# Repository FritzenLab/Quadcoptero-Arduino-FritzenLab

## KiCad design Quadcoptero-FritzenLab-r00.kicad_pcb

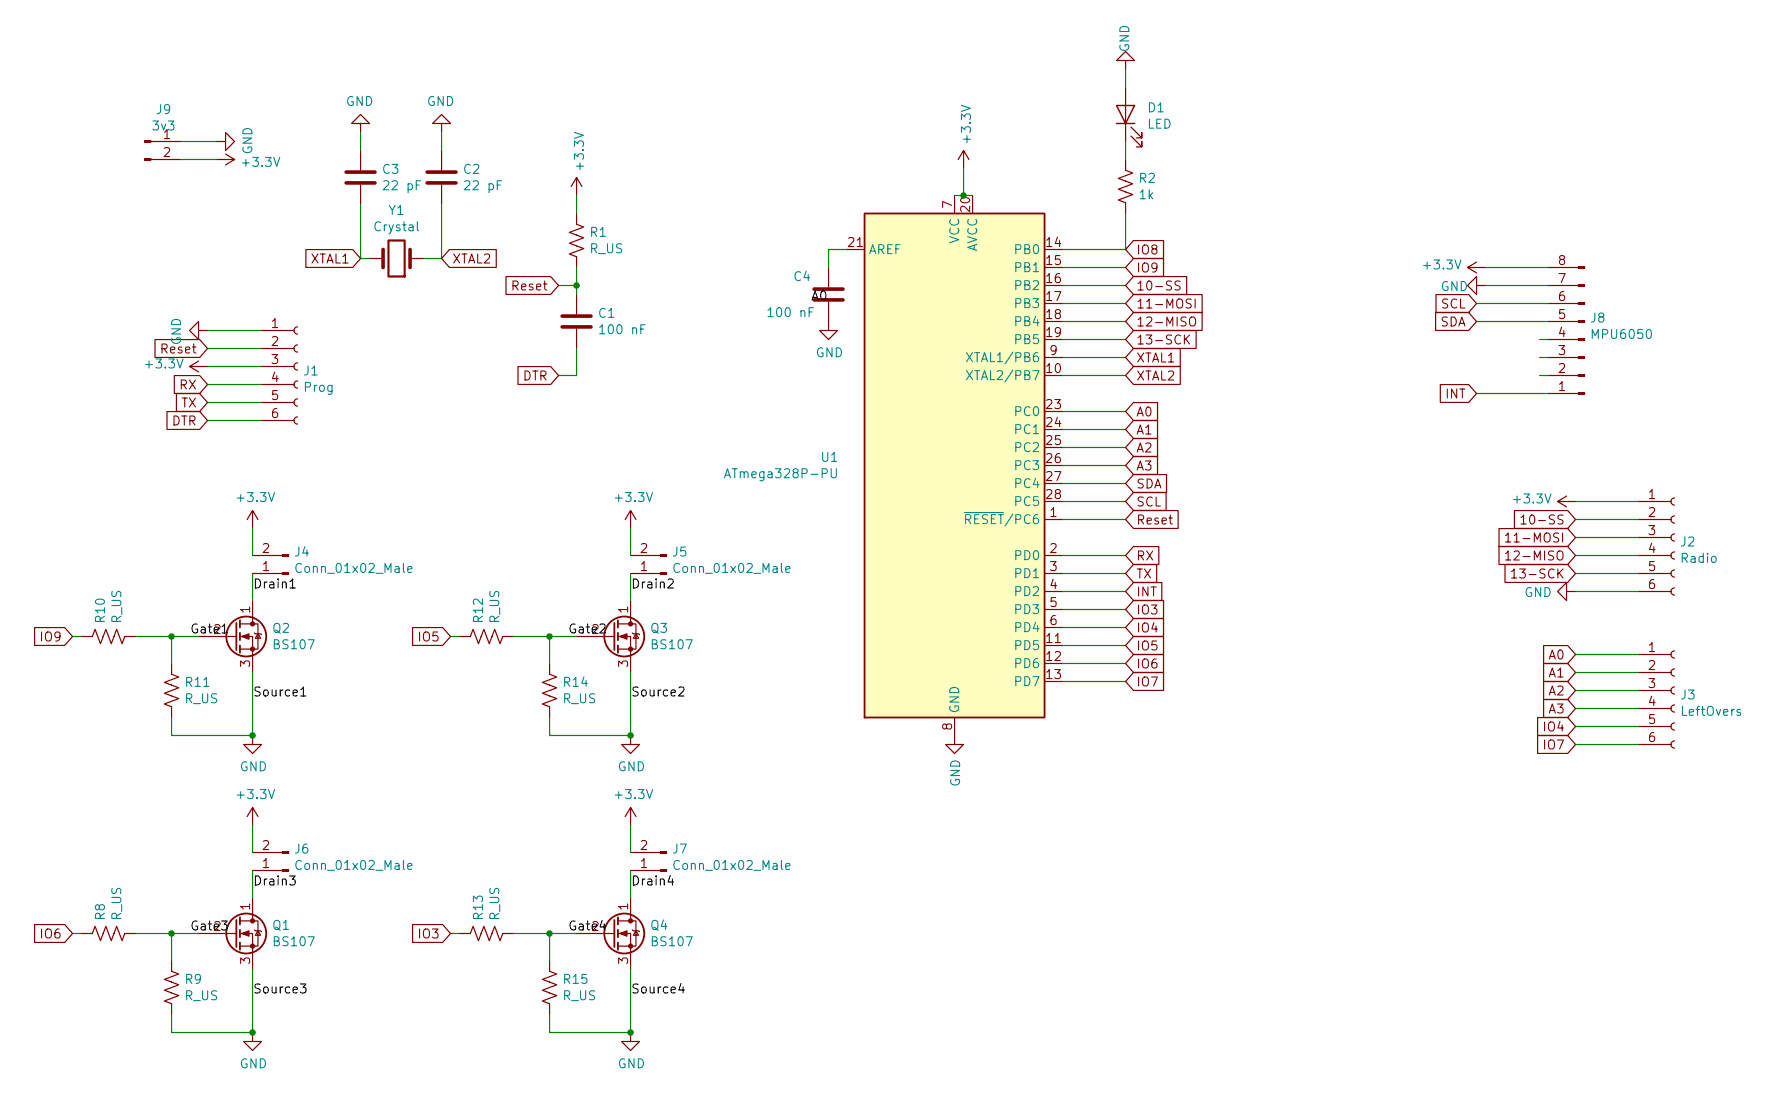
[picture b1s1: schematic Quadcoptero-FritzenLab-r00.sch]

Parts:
C1, C4: 100 nF; C_Disc_D3.0mm_W1.6mm_P2.50mm
C2, C3: 22 pF; C_Disc_D3.0mm_W1.6mm_P2.50mm
D1: LED; LED_D3.0mm
J1: Prog; PinHeader_1x06_P2.54mm_Vertical
J2: Radio; PinHeader_1x06_P2.54mm_Vertical
J3: LeftOvers; PinHeader_1x06_P2.54mm_Vertical
J4, J5, J6, J7: Conn_01x02_Male; PinSocket_1x02_P2.54mm_Vertical
J8: MPU6050; PinHeader_1x08_P2.54mm_Vertical
J9: 3v3; PinHeader_1x02_P2.00mm_Vertical
Q1, Q2, Q3, Q4: BS107; SOT-23W
R1, R8, R9, R10, R11, R12, R13, R14, R15: R_US; R_0805_2012Metric_Pad1.15x1.40mm_HandSolder
R2: 1k; R_0805_2012Metric_Pad1.15x1.40mm_HandSolder
U1: ATmega328P-PU; DIP-28_W7.62mm
Y1: Crystal; Crystal_HC50_Vertical

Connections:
10-SS: J2.2, U1.16 (PB2)
11-MOSI: J2.3, U1.17 (PB3)
12-MISO: J2.4, U1.18 (PB4)
13-SCK: J2.5, U1.19 (PB5)
+3V3: J1.3, J2.1, J4.2, J5.2, J6.2, J7.2, J8.8, J9.2, R1.1, U1.7 (VCC), U1.20 (AVCC)
/Drain1: J4.1, Q2.1 (D)
/Drain2: J5.1, Q3.1 (D)
/Drain3: J6.1, Q1.1 (D)
/Drain4: J7.1, Q4.1 (D)
/Gate1: Q2.2 (G), R10.2, R11.1
/Gate2: Q3.2 (G), R12.2, R14.1
/Gate3: Q1.2 (G), R8.2, R9.1
/Gate4: Q4.2 (G), R13.2, R15.1
A0: J3.1, U1.23 (PC0)
A1: J3.2, U1.24 (PC1)
A2: J3.3, U1.25 (PC2)
A3: J3.4, U1.26 (PC3)
DTR: C1.2, J1.6
GND: C2.1, C3.1, C4.2, D1.2 (A), J1.1, J2.6, J8.7, J9.1, Q1.3 (S), Q2.3 (S), Q3.3 (S), Q4.3 (S), R9.2, R11.2, R14.2, R15.2, U1.8 (GND), U1.22 (GND)
INT: J8.1, U1.4 (PD2)
IO3: R13.1, U1.5 (PD3)
IO4: J3.5, U1.6 (PD4)
IO5: R12.1, U1.11 (PD5)
IO6: R8.1, U1.12 (PD6)
IO7: J3.6, U1.13 (PD7)
IO8: R2.2, U1.14 (PB0)
IO9: R10.1, U1.15 (PB1)
unnamed: C4.1, U1.21 (AREF)
unnamed: D1.1 (K), R2.1
RX: J1.4, U1.2 (PD0)
Reset: C1.1, J1.2, R1.2, U1.1 (~RESET~/PC6)
SCL: J8.6, U1.28 (PC5)
SDA: J8.5, U1.27 (PC4)
TX: J1.5, U1.3 (PD1)
XTAL1: C3.2, U1.9 (XTAL1/PB6), Y1.2
XTAL2: C2.2, U1.10 (XTAL2/PB7), Y1.1

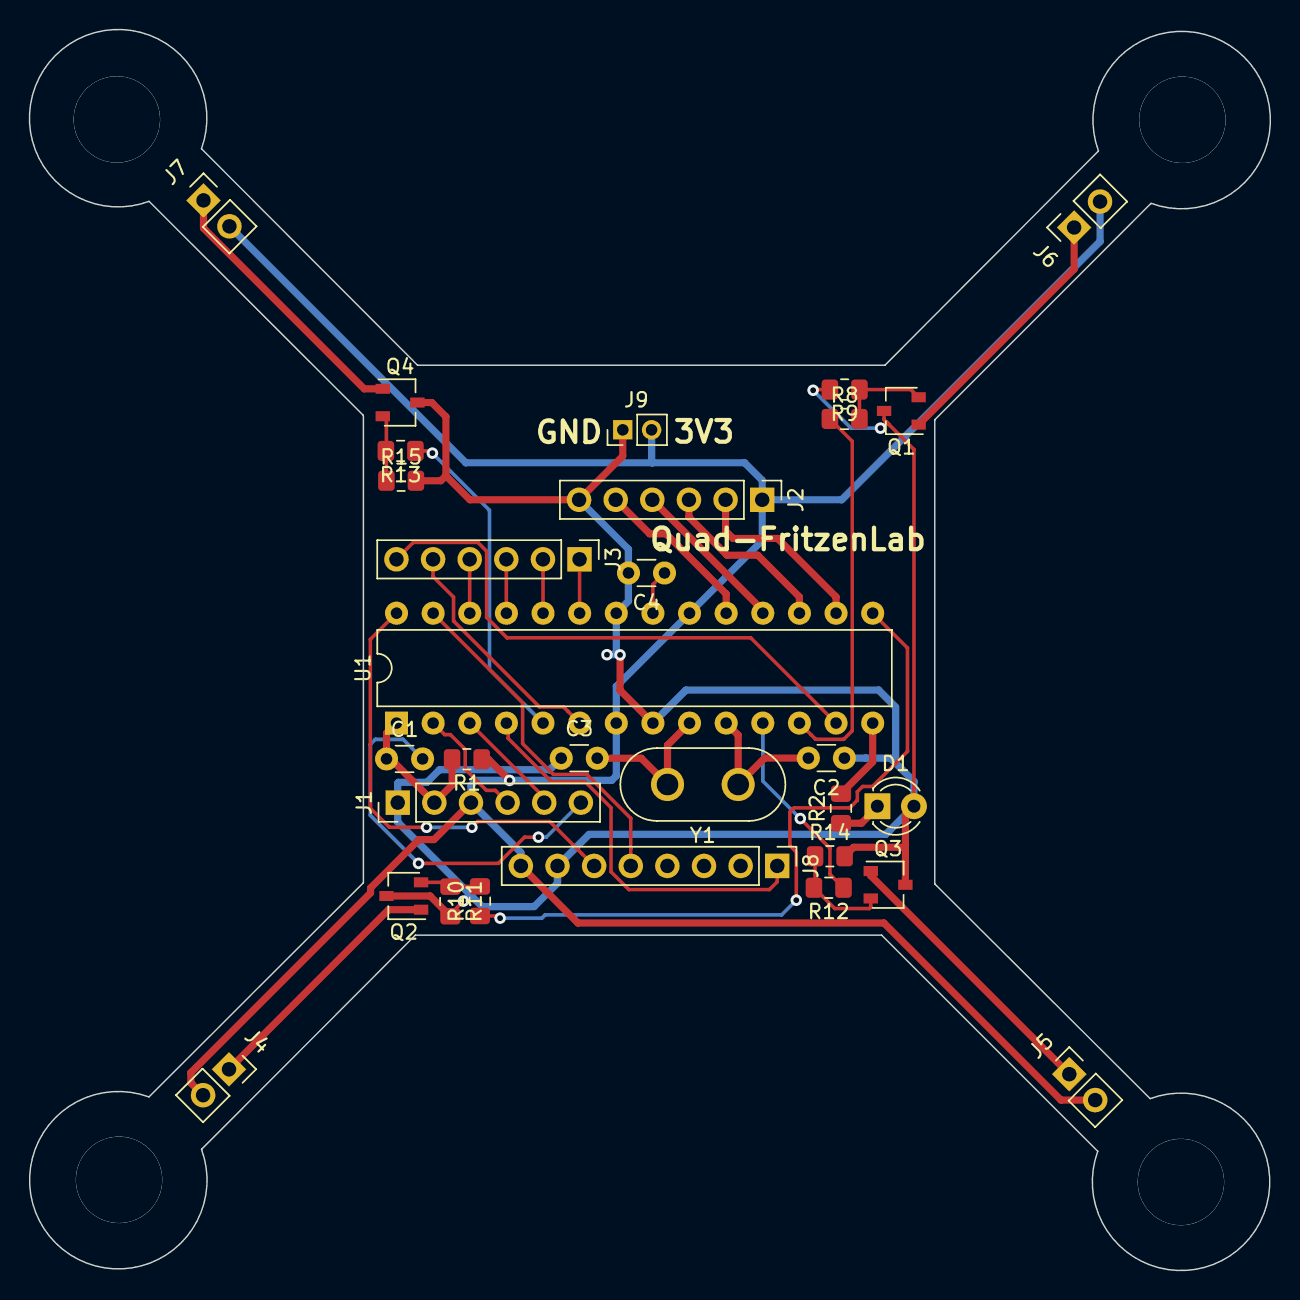
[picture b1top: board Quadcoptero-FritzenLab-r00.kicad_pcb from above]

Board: 2 copper layers, 86.0 x 86.0 mm, 30 parts (0 on the bottom side), 36 nets.

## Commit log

2019-05-17 primeiro envio de arquivos
2024-06-11 nothing edited
2024-06-21 Kicad backup files
